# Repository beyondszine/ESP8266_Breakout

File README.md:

# ESP8266_Breakout
this is breakout board for ESP8266 12E.  Based on Kicad Project

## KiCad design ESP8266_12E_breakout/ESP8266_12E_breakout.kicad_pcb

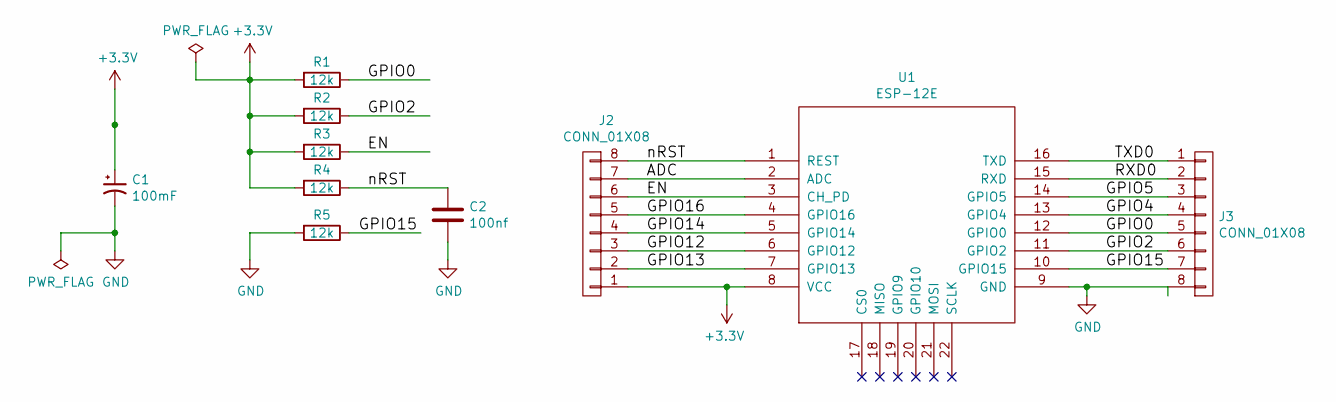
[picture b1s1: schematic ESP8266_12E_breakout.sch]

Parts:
C1: 100mF; CP_Radial_D5.0mm_P2.50mm
C2: 100nf; C_Disc_D3.0mm_W1.6mm_P2.50mm
J2, J3: CONN_01X08; Pin_Header_Straight_1x08_Pitch2.54mm
R1, R2, R3, R4, R5: 12k; R_Axial_DIN0207_L6.3mm_D2.5mm_P7.62mm_Horizontal
U1: ESP-12E; ESP-12E_SMD

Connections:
+3V3: C1.1, J2.1, R1.2, R2.2, R3.2, R4.2, U1.8 (VCC)
/ADC: J2.7, U1.2 (ADC)
/EN: J2.6, R3.1, U1.3 (CH_PD)
/GPIO0: J3.5, R1.1, U1.12 (GPIO0)
/GPIO2: J3.6, R2.1, U1.11 (GPIO2)
/GPIO4: J3.4, U1.13 (GPIO4)
/GPIO5: J3.3, U1.14 (GPIO5)
/GPIO12: J2.3, U1.6 (GPIO12)
/GPIO13: J2.2, U1.7 (GPIO13)
/GPIO14: J2.4, U1.5 (GPIO14)
/GPIO15: J3.7, R5.1, U1.10 (GPIO15)
/GPIO16: J2.5, U1.4 (GPIO16)
/RXD0: J3.2, U1.15 (RXD)
/TXD0: J3.1, U1.16 (TXD)
/nRST: C2.1, J2.8, R4.1, U1.1 (REST)
GND: C1.2, C2.2, J3.8, R5.2, U1.9 (GND)

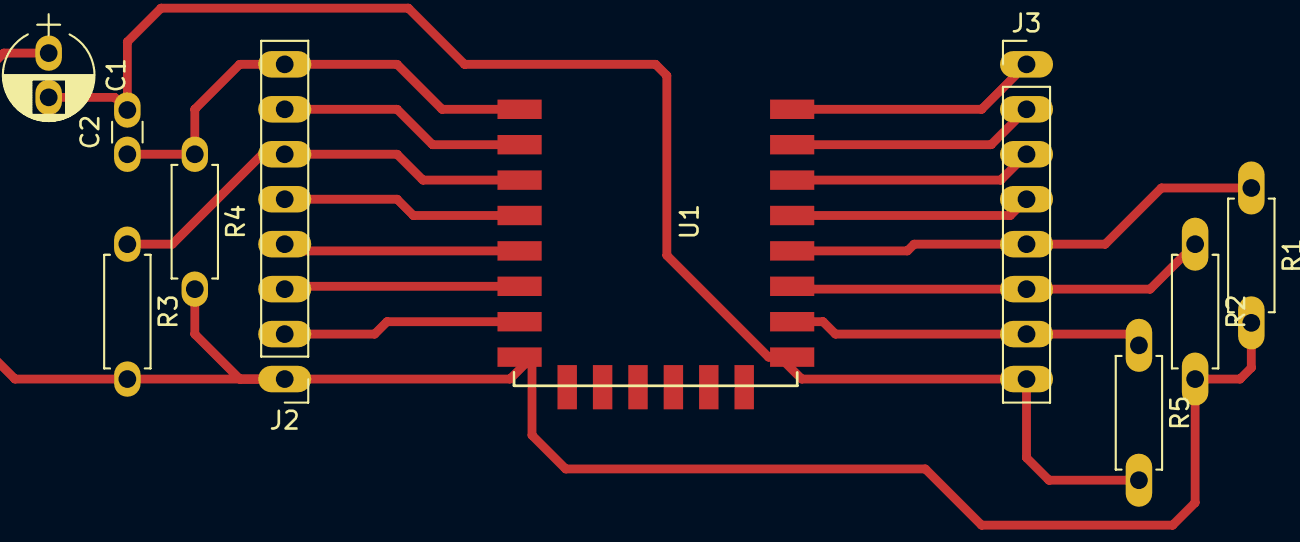
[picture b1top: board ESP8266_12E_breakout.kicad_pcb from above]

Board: 2 copper layers, 10 parts (0 on the bottom side), 16 nets.

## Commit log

2017-08-22 added basic ESP8266 12E gpio circuit
2017-08-22 updated footprints
2017-08-24 completed layout for breakout
2017-08-25 added images
2017-08-25 udpated readme with imgs
2017-08-25 pushed pad size to accomodate more solder area
2017-08-25 added pdfs for schematic & layout
